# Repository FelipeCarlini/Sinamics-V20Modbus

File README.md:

# Sinamics-V20Modbus
Sinamics-V20 drive modbus controlled by arduino mega board

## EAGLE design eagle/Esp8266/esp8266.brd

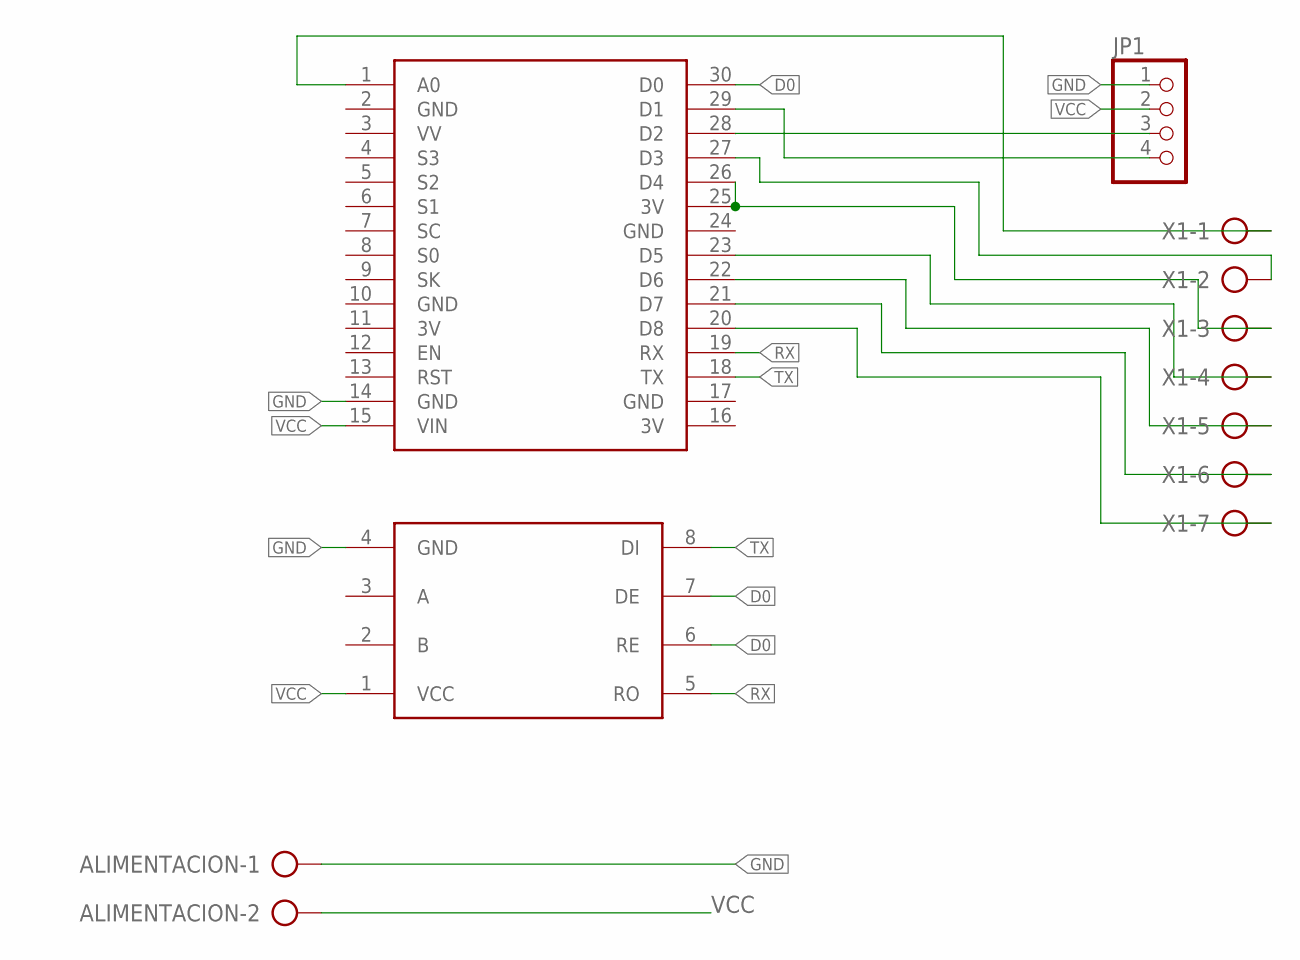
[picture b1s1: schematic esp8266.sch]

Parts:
ALIMENTACION: AK300/2
JP1: PINHD-1X4; 1X04
U$1: RS485DEVICE; 1X01
U$2: NODEMCU
X1: AK300/7

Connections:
3V: U$2.11 (3V), U$2.16 (3V)
D0: U$1.6 (RE), U$1.7 (DE), U$2.30 (D0)
GND: ALIMENTACION.1, JP1.1, U$1.4 (GND), U$2.2 (GND), U$2.10 (GND), U$2.14 (GND), U$2.17 (GND), U$2.24 (GND)
unnamed: JP1.3, U$2.28 (D2)
unnamed: JP1.4, U$2.29 (D1)
unnamed: U$2.1 (A0), X1.1
unnamed: U$2.27 (D3), X1.2
unnamed: U$2.25 (3V), U$2.26 (D4), X1.3
unnamed: U$2.23 (D5), X1.4
unnamed: U$2.22 (D6), X1.5
unnamed: U$2.21 (D7), X1.6
unnamed: U$2.20 (D8), X1.7
RX: U$1.5 (RO), U$2.19 (RX)
TX: U$1.8 (DI), U$2.18 (TX)
VCC: ALIMENTACION.2, JP1.2, U$1.1 (VCC), U$2.15 (VIN)

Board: 2 copper layers, 5 parts (0 on the bottom side), 15 nets, no tracks yet.

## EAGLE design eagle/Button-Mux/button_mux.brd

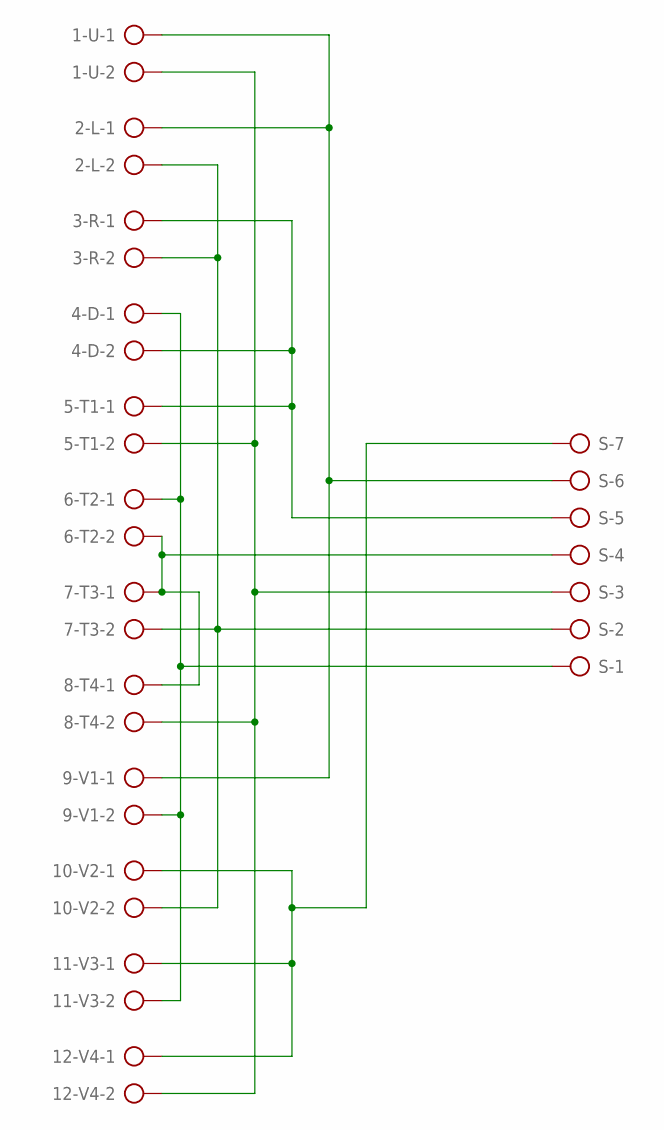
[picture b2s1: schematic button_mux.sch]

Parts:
1-U, 2-L, 3-R, 4-D, 5-T1, 6-T2, 7-T3, 8-T4, 9-V1, 10-V2, 11-V3, 12-V4: AK300/2
S: AK300/7

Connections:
unnamed: 4-D.1, 6-T2.1, 9-V1.2, 11-V3.2, S.1
unnamed: 2-L.2, 3-R.2, 7-T3.2, 10-V2.2, S.2
unnamed: 1-U.2, 5-T1.2, 8-T4.2, 12-V4.2, S.3
unnamed: 6-T2.2, 7-T3.1, 8-T4.1, S.4
unnamed: 3-R.1, 4-D.2, 5-T1.1, S.5
unnamed: 1-U.1, 2-L.1, 9-V1.1, S.6
unnamed: 10-V2.1, 11-V3.1, 12-V4.1, S.7

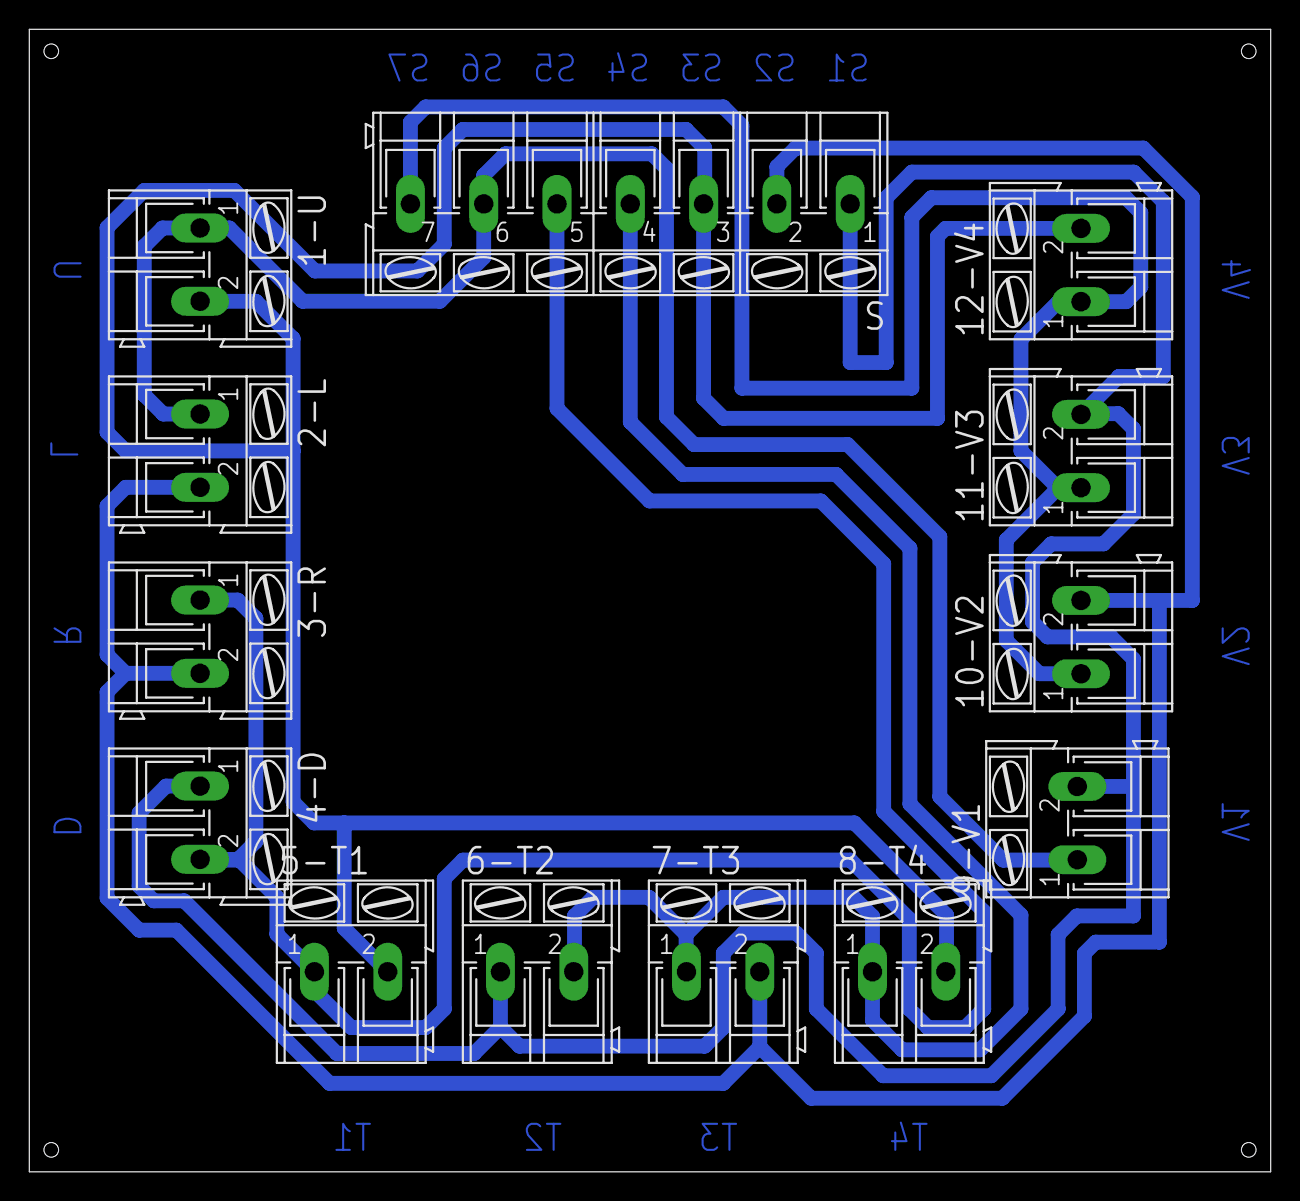
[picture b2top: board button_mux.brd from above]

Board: 2 copper layers, 84.8 x 78.0 mm, 13 parts (0 on the bottom side), 7 nets.

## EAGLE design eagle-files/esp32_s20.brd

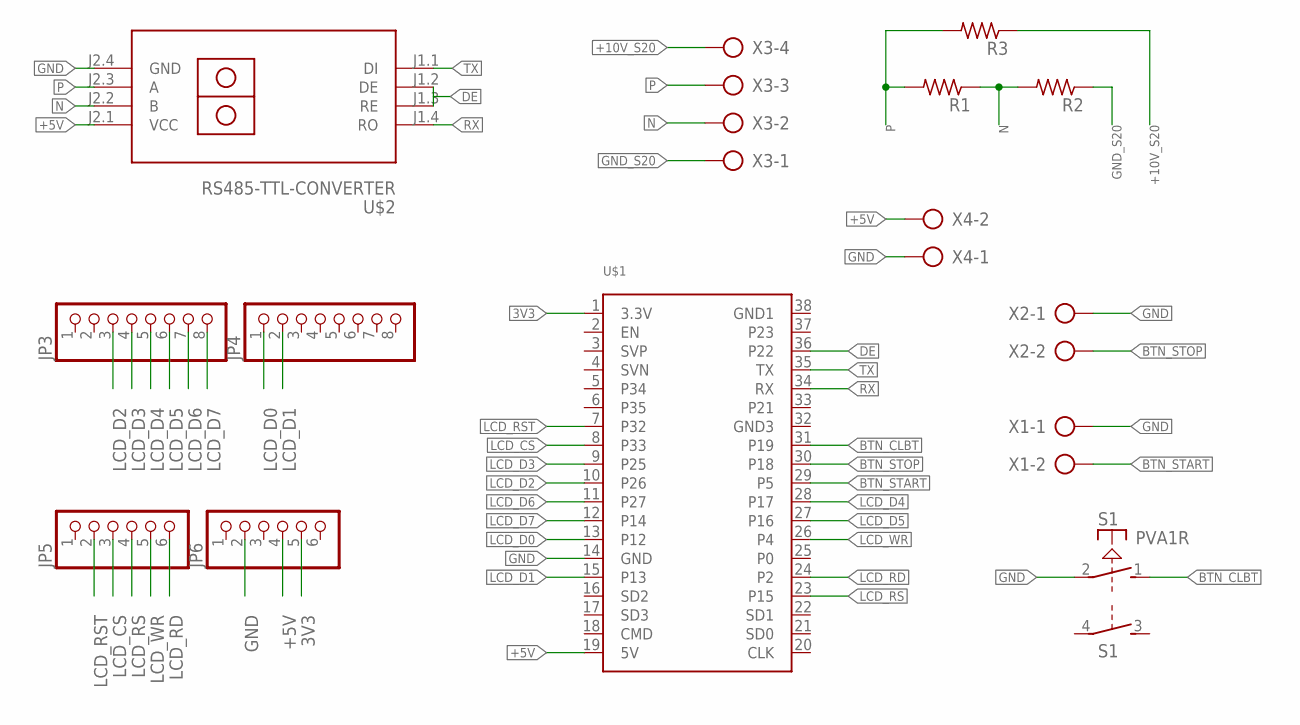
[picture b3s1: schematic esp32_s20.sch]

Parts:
JP3, JP4: PINHD-1X8; 1X08
JP5, JP6: PINHD-1X6; 1X06
R1, R2, R3: R-US_0204/7; 0204/7
S1: PVA1R
U$1: ESP-32S; BOARD
U$2: RS485-TTL-CONVERTER
X1, X2, X4: AK500/2-H
X3: AK500/4-H

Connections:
3V3: JP6.5, U$1.1 (3.3V)
+5V: JP6.4, U$1.19 (5V), U$2.J2.1 (VCC), X4.2
+10V_S20: R3.1, X3.4
BTN_CLBT: S1.1 (S), U$1.31 (P19)
BTN_START: U$1.29 (P5), X1.2
BTN_STOP: U$1.30 (P18), X2.2
DE: U$1.36 (P22), U$2.J1.2 (DE), U$2.J1.3 (RE)
GND: JP6.2, S1.2, U$1.14 (GND), U$2.J2.4 (GND), X1.1, X2.1, X4.1
GND_S20: R2.1, X3.1
LCD_CS: JP5.3, U$1.8 (P33)
LCD_D0: JP4.1, U$1.13 (P12)
LCD_D1: JP4.2, U$1.15 (P13)
LCD_D2: JP3.3, U$1.10 (P26)
LCD_D3: JP3.4, U$1.9 (P25)
LCD_D4: JP3.5, U$1.28 (P17)
LCD_D5: JP3.6, U$1.27 (P16)
LCD_D6: JP3.7, U$1.11 (P27)
LCD_D7: JP3.8, U$1.12 (P14)
LCD_RD: JP5.6, U$1.24 (P2)
LCD_RS: JP5.4, U$1.23 (P15)
LCD_RST: JP5.2, U$1.7 (P32)
LCD_WR: JP5.5, U$1.26 (P4)
N: R1.1, R2.2, U$2.J2.2 (B), X3.2
P: R1.2, R3.2, U$2.J2.3 (A), X3.3
RX: U$1.34 (RX), U$2.J1.4 (RO)
TX: U$1.35 (TX), U$2.J1.1 (DI)

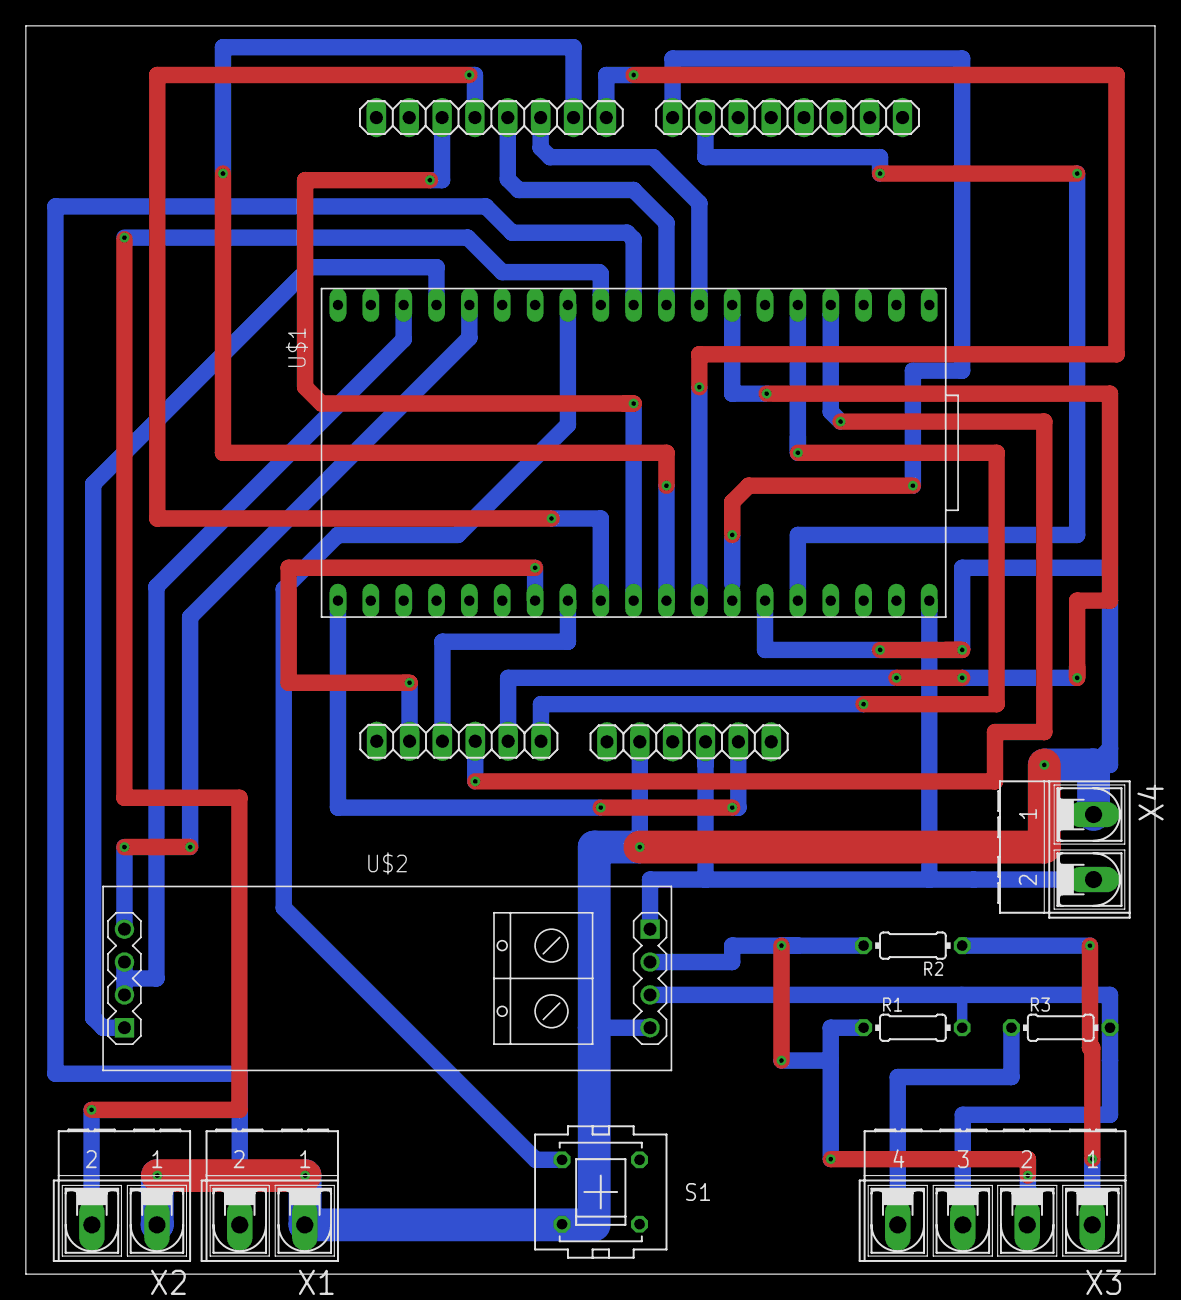
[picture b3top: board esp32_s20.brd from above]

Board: 2 copper layers, 87.3 x 96.5 mm, 14 parts (0 on the bottom side), 26 nets.

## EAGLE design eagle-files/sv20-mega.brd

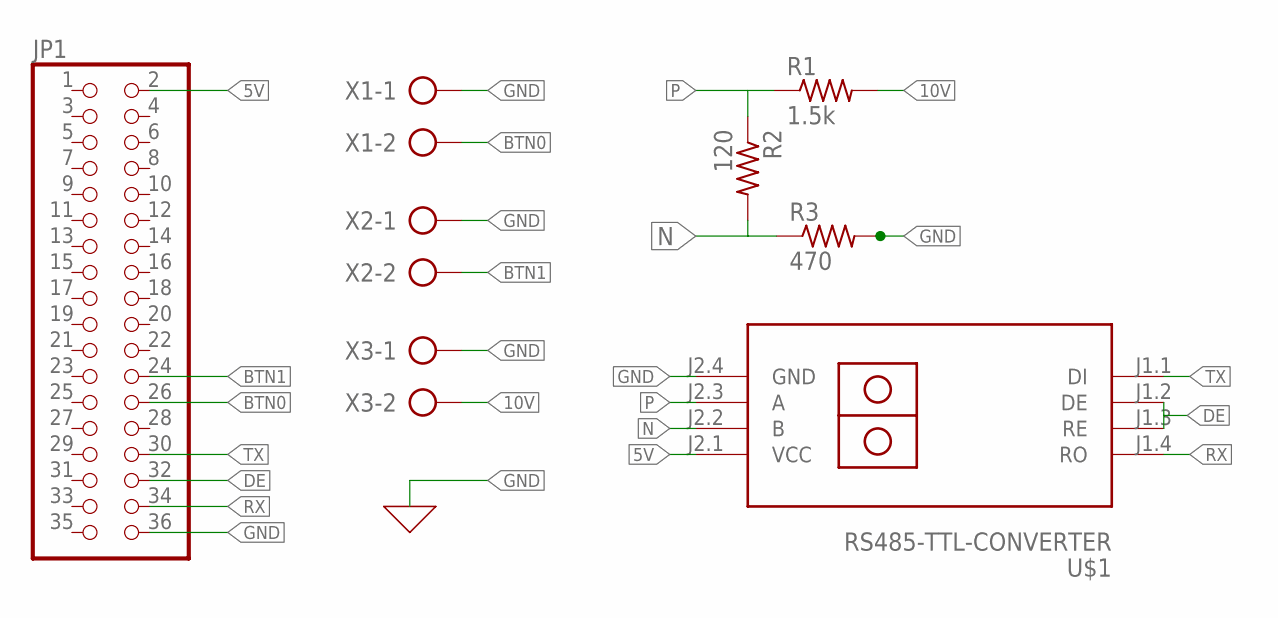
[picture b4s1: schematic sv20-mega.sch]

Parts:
JP1: PINHD-2X18; 2X18
R1: 1.5k; 0204/7
R2: 120; 0204/7
R3: 470; 0204/7
U$1: RS485-TTL-CONVERTER
X1, X2, X3: AK300/2

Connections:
5V: JP1.2, U$1.J2.1 (VCC)
10V: R1.2, X3.2
BTN0: JP1.26, X1.2
BTN1: JP1.24, X2.2
DE: JP1.32, U$1.J1.2 (DE), U$1.J1.3 (RE)
GND: JP1.36, R3.2, U$1.J2.4 (GND), X1.1, X2.1, X3.1
N: R2.2, R3.1, U$1.J2.2 (B)
P: R1.1, R2.1, U$1.J2.3 (A)
RX: JP1.34, U$1.J1.4 (RO)
TX: JP1.30, U$1.J1.1 (DI)

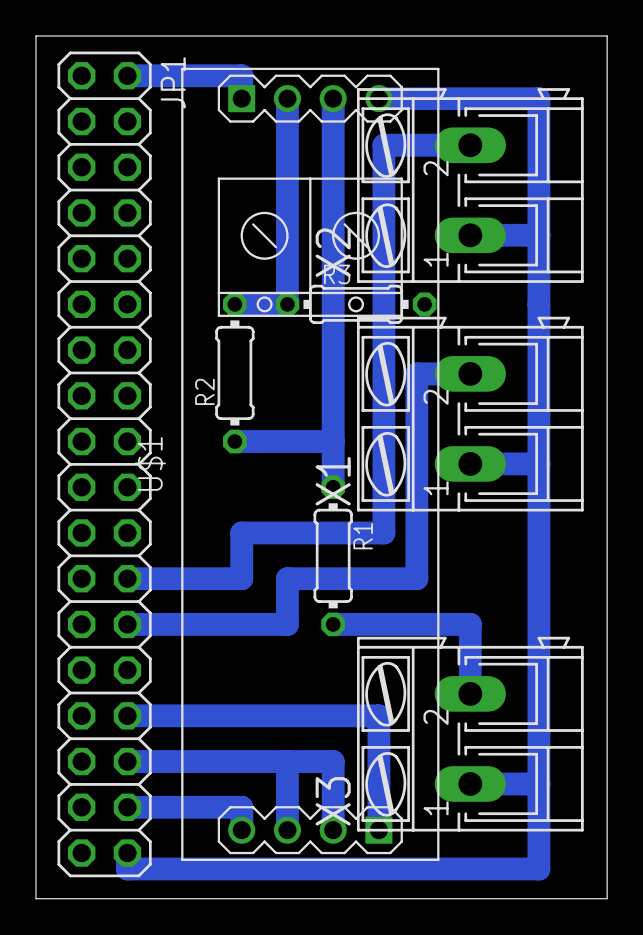
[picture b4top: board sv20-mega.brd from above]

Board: 2 copper layers, 31.7 x 47.9 mm, 8 parts (0 on the bottom side), 10 nets.

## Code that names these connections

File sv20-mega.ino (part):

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TouchScreen ts = TouchScreen(XP, YP, XM, YM, 300);

#define LCD_RESET A4
#define LCD_CS A3
#define LCD_CD A2
#define LCD_WR A1
#define LCD_RD A0

#define BLACK   0x0000
#define BLUE    0x001F
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
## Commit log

2020-04-16 [ADD] init
2020-04-16 [MOD] changed manual
2020-04-16 [MOD] mod manual
2020-04-18 [ADD] Arduino libraries
2020-04-18 Bump rack from 2.0.1 to 2.2.2 in /arduino-libraries/ModbusMaster-master
    Bumps [rack](https://github.com/rack/rack) from 2.0.1 to 2.2.2.
    - [Release notes](https://github.com/rack/rack/releases)
    - [Changelog](https://github.com/rack/rack/blob/master/CHANGELOG.md)
    - [Commits](https://github.com/rack/rack/compare/2.0.1...v2.2.2)
2020-04-19 [MOD] Gemfile
2020-04-19 Bump rake in /arduino-libraries/ModbusMaster-master
    Bumps [rake](https://github.com/ruby/rake) from 11.2.2 to 12.3.3.
    - [Release notes](https://github.com/ruby/rake/releases)
    - [Changelog](https://github.com/ruby/rake/blob/master/History.rdoc)
    - [Commits](https://github.com/ruby/rake/compare/v11.2.2...v12.3.3)
2020-04-29 [ADD] eagle files
2020-06-24 Bump rack from 2.2.2 to 2.2.3 in /arduino-libraries/ModbusMaster-master
    Bumps [rack](https://github.com/rack/rack) from 2.2.2 to 2.2.3.
    - [Release notes](https://github.com/rack/rack/releases)
    - [Changelog](https://github.com/rack/rack/blob/master/CHANGELOG.md)
    - [Commits](https://github.com/rack/rack/compare/v2.2.2...2.2.3)
2021-04-24 initial commit arduino mega
2021-05-30 [MOD] ino filename
2021-08-16 [ADD] job logic
2021-09-01 [ADD] esp32 support
2021-09-01 [REM] .pio files
2021-09-01 [ADD] TFT_eSPI/User_Setup.h file replaced pre compilation
2021-09-02 [ADD] User interface
2021-09-02 [MOD] tft setup
2021-09-02 [MOD] EEPROM cleaned if speed > 100 %
2021-09-02 [ADD] EEPROM commit after write operations
2021-09-03 [FIX] some fixes
2021-09-03 [ADD] sinamics V20 modbus driver
2021-09-08 [ADD] hardware buttons
2021-09-15 [ADD] format code
2021-09-15 [ADD] traces
2021-09-25 [MOD] update traces
2022-03-01 [MOD] project initialization scripts
2022-07-27 [ADD] last changes
2025-09-11 [MOD] update eagle files
2025-09-11 [ADD] docs

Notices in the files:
parts and their libraries:
diy-modules: Released under the Creative Commons Attribution 4.0 International License: http://creativecommons.org/licenses/by/4.0
